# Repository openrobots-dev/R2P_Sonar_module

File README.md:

R2P Sonar module
===================

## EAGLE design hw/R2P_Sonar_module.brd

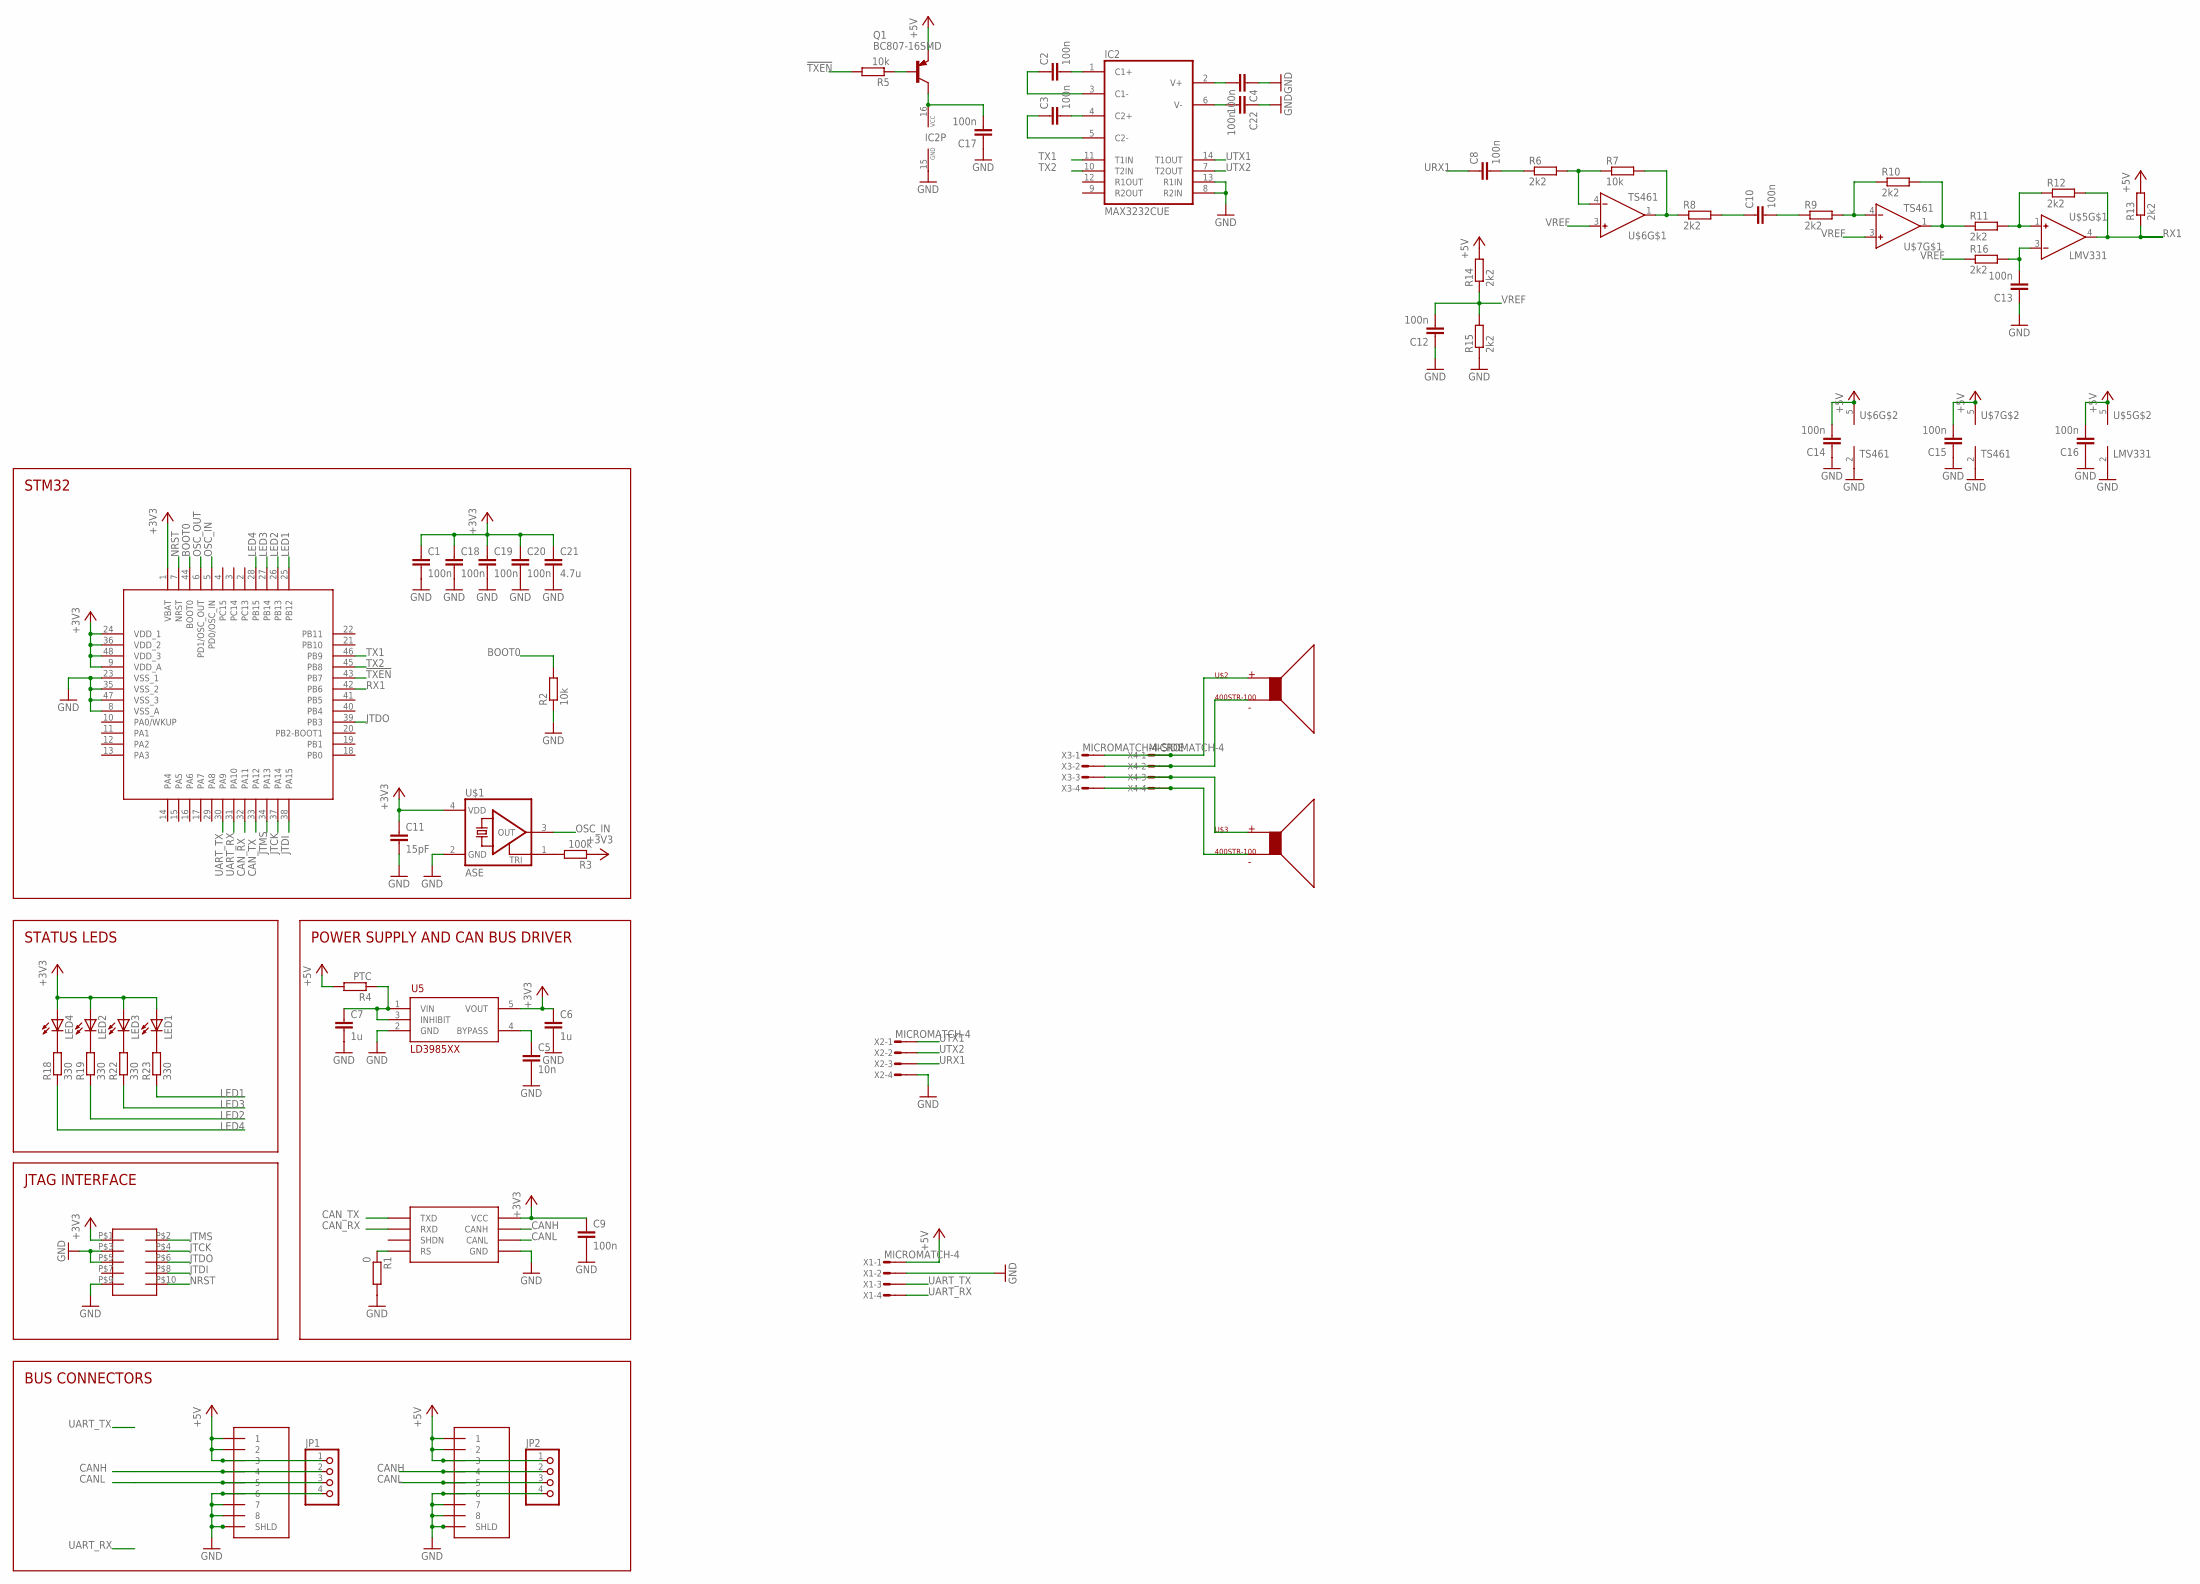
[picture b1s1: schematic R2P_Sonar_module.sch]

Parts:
1, 2: RJ45-43860; 0438600010
C1, C2, C3, C4, C8, C9, C10, C12, C13, C14, C15, C16, C17, C18, C19, C20, C22: 100n; C0603
C5: 10n; C0603
C6, C7: 1u; C0603
C11: 15pF; C0603
C21: 4.7u; C0805
IC2: MAX3232CUE; TSSOP16
JP1, JP2: PINHD-1X4; 1X04
LED1, LED2, LED3, LED4: LEDCHIPLED_0805; CHIPLED_0805
Q1: BC807-16SMD; SOT23-BEC
R1: 0; R0603
R2, R5, R7: 10k; R0603
R3: 100k; R0603
R4: PTC; R0603
R6, R8, R9, R10, R11, R12, R13, R14, R15, R16: 2k2; R0603
R18, R19, R22, R23: 330; R0603
SOT1: MAX3051; SOT23-8L
U1: STM32F103CX; LQFP48
U5: LD3985XX; SOT23-5L
U$1: ASE
U$2, U$3: 400STR-100; 400STR100
U$4: FTSH-105
U$5: LMV331; SOT23-5L
U$6, U$7: TS461; SOT23-5L
X1, X2, X4: MICROMATCH-4
X3: MICROMATCH-4-SIDE

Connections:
!TXEN: R5.2, U1.43 (PB7)
+3V3: C1.1, C6.1, C9.1, C11.1, C18.1, C19.1, C20.1, C21.1, LED1.A, LED2.A, LED3.A, LED4.A, R3.1, SOT1.P$3 (VCC), U1.1 (VBAT), U1.9 (VDD_A), U1.24 (VDD_1), U1.36 (VDD_2), U1.48 (VDD_3), U5.5 (VOUT), U$1.4 (VDD), U$4.P$1
+5V: 1.P$1 (1), 1.P$2 (2), 1.P$3 (3), 2.P$1 (1), 2.P$2 (2), 2.P$3 (3), C14.2, C15.2, C16.2, JP1.1, JP2.1, Q1.E, R4.2, R13.2, R14.2, U$5.5 (V+), U$6.5 (V+), U$7.5 (V+), X1.1
BOOT0: R2.2, U1.44 (BOOT0)
CANH: 1.P$4 (4), 2.P$4 (4), JP1.2, JP2.2, SOT1.P$7 (CANH)
CANL: 1.P$5 (5), 2.P$5 (5), JP1.3, JP2.3, SOT1.P$6 (CANL)
CAN_RX: SOT1.P$4 (RXD), U1.32 (PA11)
CAN_TX: SOT1.P$1 (TXD), U1.33 (PA12)
GND: 1.P$6 (6), 1.P$7 (7), 1.P$8 (8), 1.P$9 (SHLD), 1.P$10, 2.P$6 (6), 2.P$7 (7), 2.P$8 (8), 2.P$9 (SHLD), 2.P$10, C1.2, C4.1, C5.2, C6.2, C7.2, C9.2, C11.2, C12.1, C13.1, C14.1, C15.1, C16.1, C17.1, C18.2, C19.2, C20.2, C21.2, C22.1, IC2.8 (R2IN), IC2.13 (R1IN), IC2.15 (GND), JP1.4, JP2.4, R1.2, R2.1, R15.1, SOT1.P$2 (GND), U1.8 (VSS_A), U1.23 (VSS_1), U1.35 (VSS_2), U1.47 (VSS_3), U5.2 (GND), U$1.2 (GND), U$4.P$3, U$4.P$5, U$4.P$9, U$5.2 (V-), U$6.2 (V-), U$7.2 (V-), X1.2, X2.4
JTCK: U1.37 (PA14), U$4.P$4
JTDI: U1.38 (PA15), U$4.P$8
JTDO: U1.39 (PB3), U$4.P$6
JTMS: U1.34 (PA13), U$4.P$2
LED1: R23.1, U1.25 (PB12)
LED2: R19.1, U1.26 (PB13)
LED3: R22.1, U1.27 (PB14)
LED4: R18.1, U1.28 (PB15)
unnamed: R1.1, SOT1.P$8 (RS)
unnamed: R3.2, U$1.1 (TRI)
unnamed: C5.1, U5.4 (BYPASS)
unnamed: C7.1, R4.1, U5.1 (VIN), U5.3 (INHIBIT)
unnamed: C2.2, IC2.1 (C1+)
unnamed: C2.1, IC2.3 (C1-)
unnamed: C3.2, IC2.4 (C2+)
unnamed: C3.1, IC2.5 (C2-)
unnamed: C17.2, IC2.16 (VCC), Q1.C
unnamed: C8.2, R6.1
unnamed: U$2.P$1, X3.1, X4.1
unnamed: U$2.P$2, X3.2, X4.2
unnamed: U$3.P$1, X3.3, X4.3
unnamed: LED4.C, R18.2
unnamed: U$3.P$2, X3.4, X4.4
unnamed: Q1.B, R5.1
unnamed: LED2.C, R19.2
unnamed: LED3.C, R22.2
unnamed: R6.2, R7.1, U$6.4 (IN-)
unnamed: LED1.C, R23.2
unnamed: R7.2, R8.1, U$6.1 (OUT)
unnamed: C10.1, R8.2
unnamed: C10.2, R9.1
unnamed: R9.2, R10.1, U$7.4 (IN-)
unnamed: R10.2, R11.1, U$7.1 (OUT)
unnamed: R11.2, R12.1, U$5.1 (IN+)
unnamed: C4.2, IC2.2 (V+)
unnamed: C13.2, R16.2, U$5.3 (IN-)
unnamed: C22.2, IC2.6 (V-)
NRST: U1.7 (NRST), U$4.P$10
OSC_IN: U1.5 (PD0/OSC_IN), U$1.3 (OUT)
OSC_OUT: U1.6 (PD1/OSC_OUT)
RX1: R12.2, R13.1, U1.42 (PB6), U$5.4 (OUT)
TX1: IC2.11 (T1IN), U1.46 (PB9)
TX2: IC2.10 (T2IN), U1.45 (PB8)
UART_RX: U1.31 (PA10), X1.4
UART_TX: U1.30 (PA9), X1.3
URX1: C8.1, X2.3
UTX1: IC2.14 (T1OUT), X2.1
UTX2: IC2.7 (T2OUT), X2.2
VREF: C12.2, R14.1, R15.2, R16.1, U$6.3 (IN+), U$7.3 (IN+)

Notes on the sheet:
STM32
POWER SUPPLY AND CAN BUS DRIVER
STATUS LEDS
JTAG INTERFACE
BUS CONNECTORS

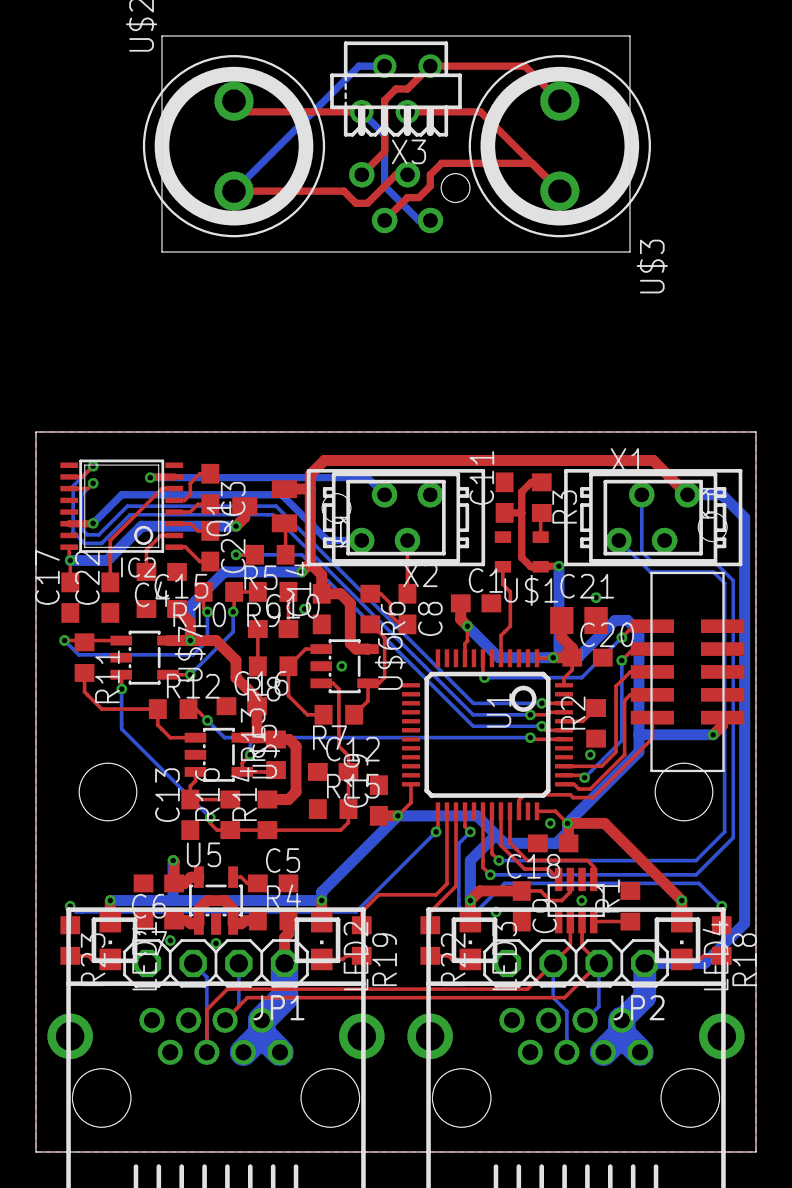
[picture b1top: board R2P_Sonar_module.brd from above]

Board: 2 copper layers, 40.0 x 62.0 mm, 66 parts (1 on the bottom side), 57 nets.

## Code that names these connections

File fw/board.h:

/*
 ChibiOS/RT - Copyright (C) 2006,2007,2008,2009,2010,
 2011 Giovanni Di Sirio.

 This file is part of ChibiOS/RT.

 ChibiOS/RT is free software; you can redistribute it and/or modify
 it under the terms of the GNU General Public License as published by
 the Free Software Foundation; either version 3 of the License, or
 (at your option) any later version.

 ChibiOS/RT is distributed in the hope that it will be useful,
 but WITHOUT ANY WARRANTY; without even the implied warranty of
 MERCHANTABILITY or FITNESS FOR A PARTICULAR PURPOSE.  See the
 GNU General Public License for more details.

 You should have received a copy of the GNU General Public License
 along with this program.  If not, see <http://www.gnu.org/licenses/>.
 */

#ifndef _BOARD_H_
#define _BOARD_H_

/*
 * Setup for the R2P Sonar module.
 */

/*
 * Board identifier.
 */
#define BOARD_R2P_SONAR_MODULE
#define BOARD_NAME              "R2P Sonar module"

/*
 * Board frequencies.
 */
#define STM32_LSECLK            32768
#define STM32_HSECLK            8000000

/*
 * MCU type, supported types are defined in ./os/hal/platforms/hal_lld.h.
 */
#define STM32F10X_MD

/*
 * IO pins assignments.
 */
#define LED_GPIO				GPIOB
#define LED1					12
#define LED2					13
#define LED3					14
#define LED4					15

#define MAX3232_GPIO			GPIOB
#define MAX3232_EN				7

#define ECHO                   6

#define SERIAL_DRIVER           SD1
#define PWM_DRIVER              PWMD4
#define GPT_DRIVER              GPTD2
#define EXT_DRIVER              EXTD1

/*
 * I/O ports initial setup, this configuration is established soon after reset
 * in the initialization code.
 *
 * The digits have the following meaning:
 *   0 - Analog input.
 *   1 - Push Pull output 10MHz.
 *   2 - Push Pull output 2MHz.
 *   3 - Push Pull output 50MHz.
 *   4 - Digital input.
 *   5 - Open Drain output 10MHz.
 *   6 - Open Drain output 2MHz.
 *   7 - Open Drain output 50MHz.
 *   8 - Digital input with PullUp or PullDown resistor depending on ODR.
 *   9 - Alternate Push Pull output 10MHz.
 *   A - Alternate Push Pull output 2MHz.
 *   B - Alternate Push Pull output 50MHz.
 *   C - Reserved.
 *   D - Alternate Open Drain output 10MHz.
 *   E - Alternate Open Drain output 2MHz.
 *   F - Alternate Open Drain output 50MHz.
 * Please refer to the STM32 Reference Manual for details.
 */

/*
 * Port A setup.
 * Everything input with pull-up except:
 * PA9  - Alternate output (USART1 TX).
 * PA10 - Normal input     (USART1 RX).
 */
#define VAL_GPIOACRL            0x88888888      /*  PA7...PA0 */
#define VAL_GPIOACRH            0x888884B8      /* PA15...PA8 */
#define VAL_GPIOAODR            0xFFFFFFFF

/*
 * Port B setup.
 * Everything input with pull-up except:
 *
 * PB6  - Normal input (ECHO).
 * PB7  - Push Pull output (!MAX3232_EN).
 * PB8  - Alternate output (PWM4CH3).
 * PB9  - Alternate output (PWM4CH4).
 * PB12 - Push Pull output (LED1).
 * PB13 - Push Pull output (LED2).
 * PB14 - Push Pull output (LED3).
 * PB15 - Push Pull output (LED4).
 */
#define VAL_GPIOBCRL            0x34888888      /*  PB7...PB0 */
#define VAL_GPIOBCRH            0x333388BB      /* PB15...PB8 */
#define VAL_GPIOBODR            0xFFFFFFFF

/*
 * Port C setup.
 * Everything input with pull-up except:
 */
#define VAL_GPIOCCRL            0x88888888      /*  PC7...PC0 */
#define VAL_GPIOCCRH            0x88888888      /* PC15...PC8 */
#define VAL_GPIOCODR            0xFFFFFFFF

#if !defined(_FROM_ASM_)
#ifdef __cplusplus
extern "C" {
#endif
void boardInit(void);
#ifdef __cplusplus
}
#endif
#endif /* _FROM_ASM_ */

#endif /* _BOARD_H_ */

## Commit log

2012-08-01 Rename
2012-08-01 Ongoing layout
2012-08-27 Layout complete
2013-07-05 Test firmware
